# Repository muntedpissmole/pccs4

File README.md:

# PCCS4 Demo

A self-contained demo of the Pissmole Camper Control System — runs on Linux. Lights, reed switches, Sonos, battery/solar, water, and GPS are simulated so you can explore the full web UI (lighting, scenes, home dashboard, system tab).

Reed switches open and close on their own every few hours; the Sonos tile plays through a built-in indie/alternative playlist.

## Install

```bash
git clone -b demo https://github.com/muntedpissmole/pccs4.git ~/pccs-demo
cd ~/pccs-demo
chmod +x scripts/install-demo.sh
sudo ./scripts/install-demo.sh
```

Open `http://<server-ip>:5000/` in a browser.

The installer sets up the Python venv, `requirements-demo.txt`, and a `pccs-demo` systemd service listening on port 5000.

## After install

```bash
sudo systemctl status pccs-demo
sudo journalctl -u pccs-demo -f
```

To make sure there's no errors.

## Update

Use the update script (handles `git pull`, dependency refresh, and config safely):

```bash
cd ~/pccs-demo
chmod +x scripts/update-demo.sh
sudo ./scripts/update-demo.sh
```

**Do not edit `config/pccs.conf` on the server.** The installer writes machine-specific settings (port, `debug = false`, etc.) to `config/pccs.local.conf`, which git ignores. If you need custom settings, edit `pccs.local.conf` and restart the service.

If you previously hit a `git pull` error about `config/pccs.conf`, run `update-demo.sh` once — it resets that file and pulls cleanly.

## Uninstall

Removes the systemd service, Python venv, logs, and firewall rule. The repo directory is kept — delete it manually if you no longer need it.

```bash
cd ~/pccs-demo
chmod +x scripts/uninstall-demo.sh
sudo ./scripts/uninstall-demo.sh
```

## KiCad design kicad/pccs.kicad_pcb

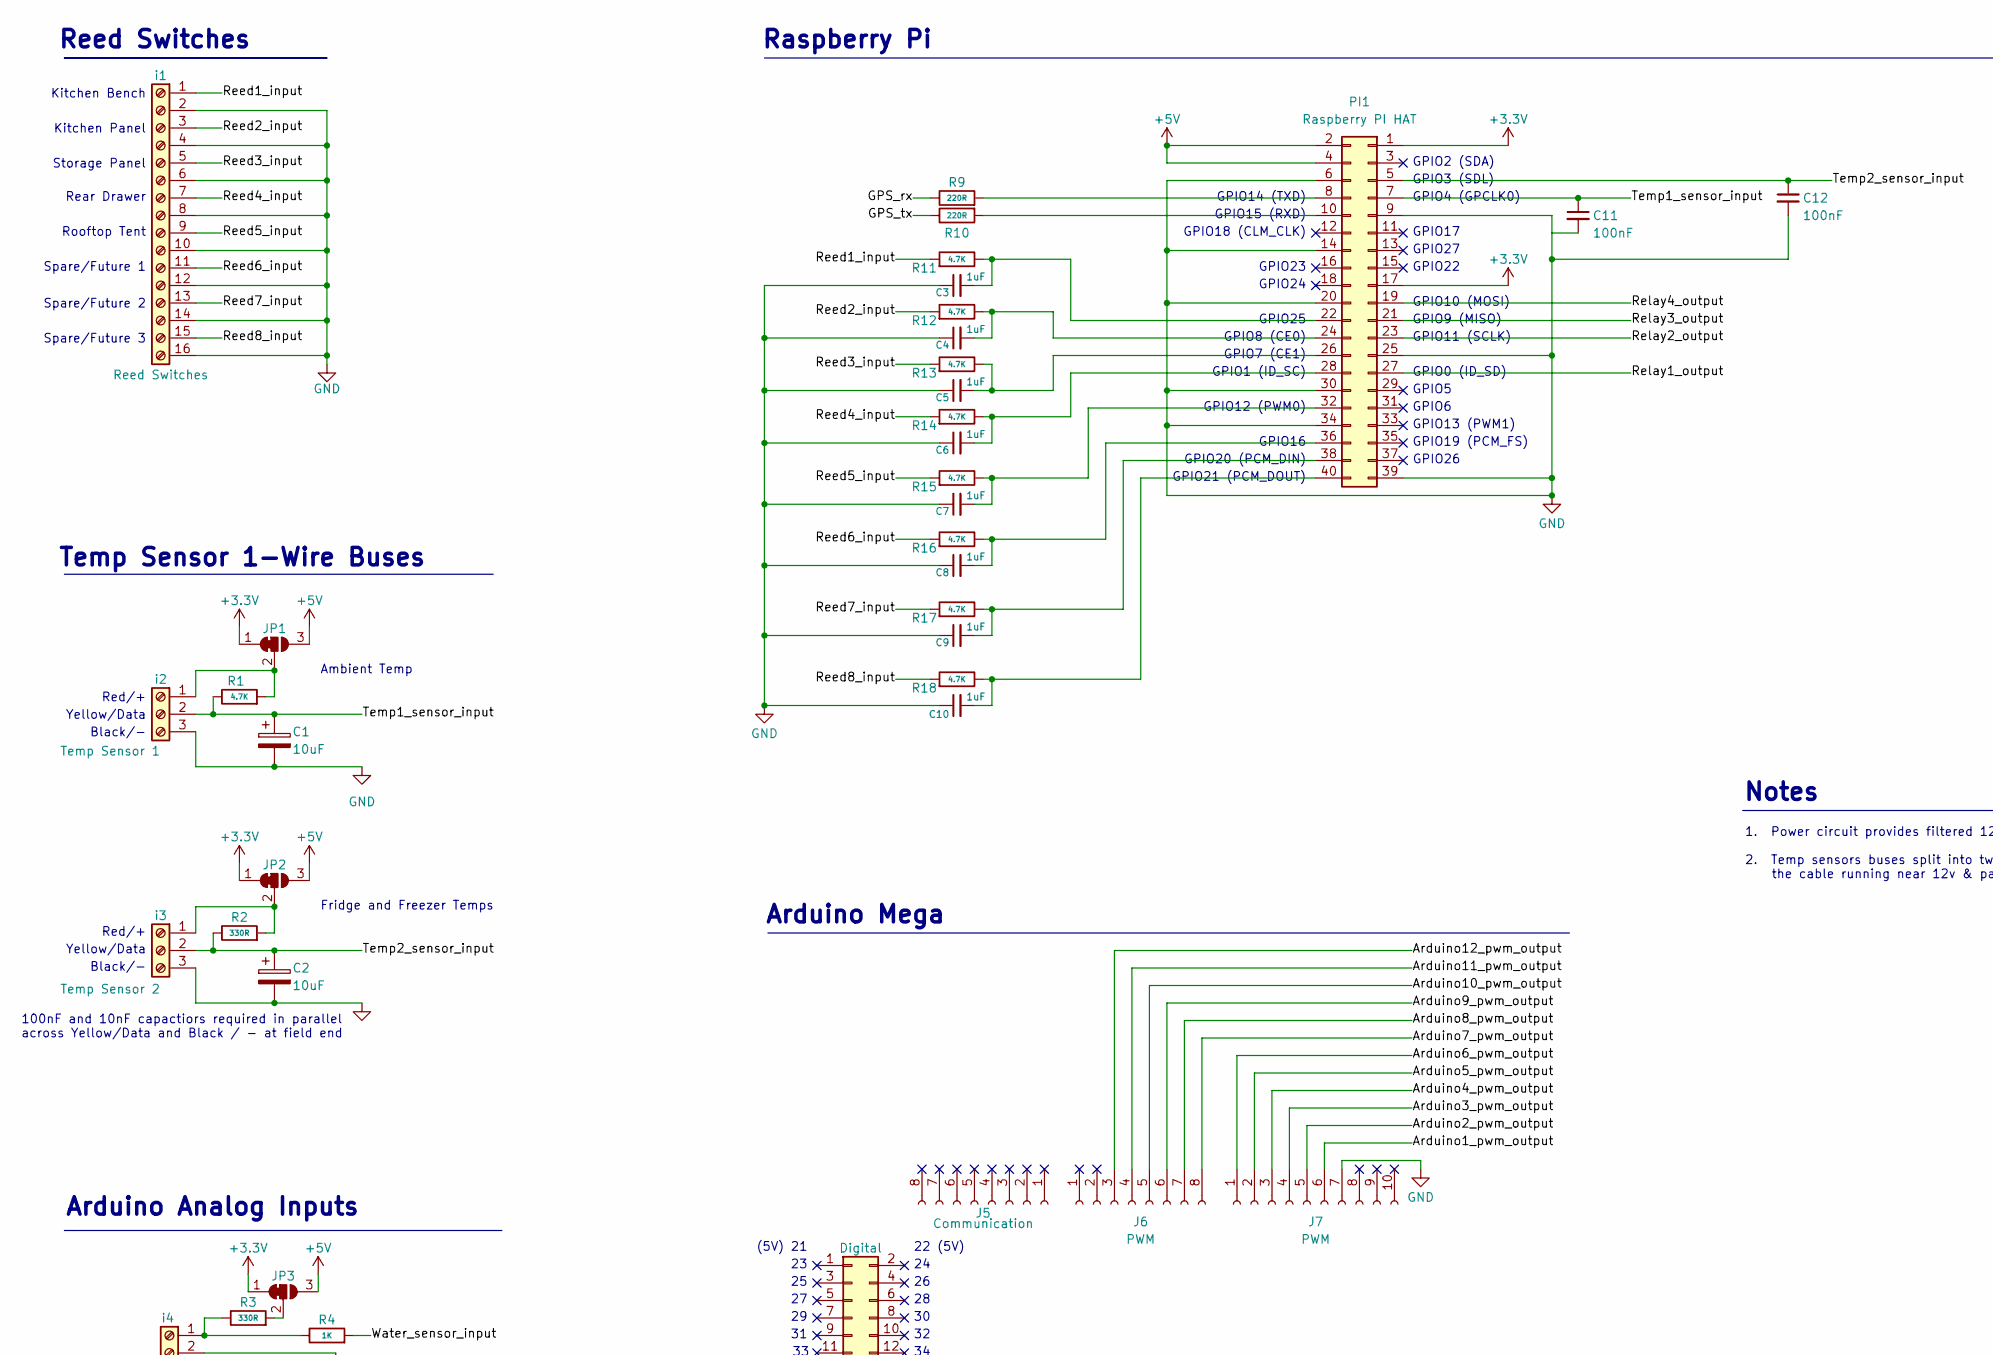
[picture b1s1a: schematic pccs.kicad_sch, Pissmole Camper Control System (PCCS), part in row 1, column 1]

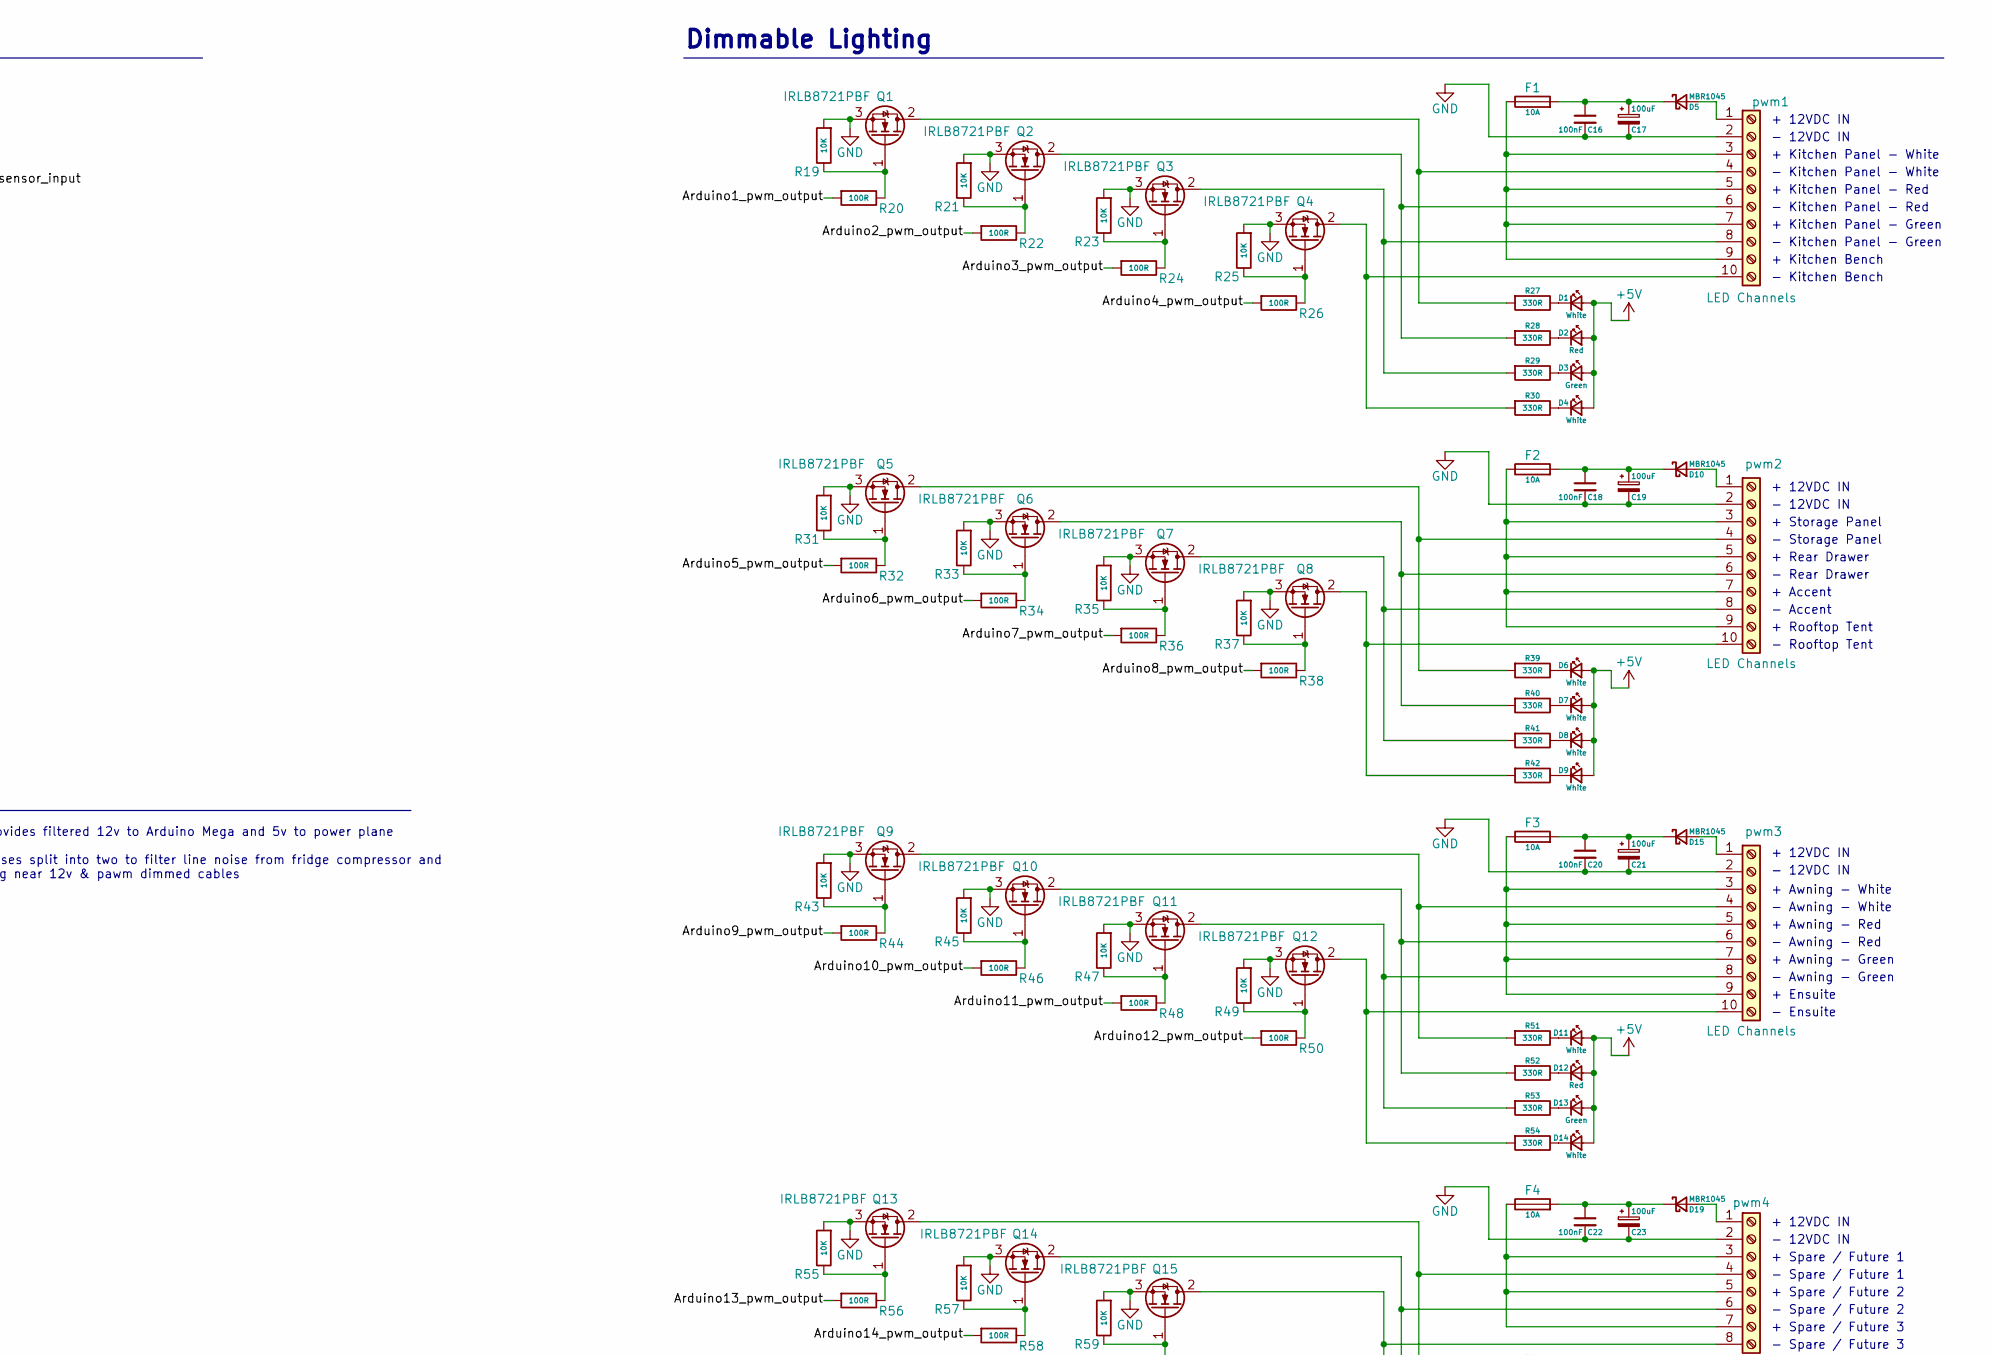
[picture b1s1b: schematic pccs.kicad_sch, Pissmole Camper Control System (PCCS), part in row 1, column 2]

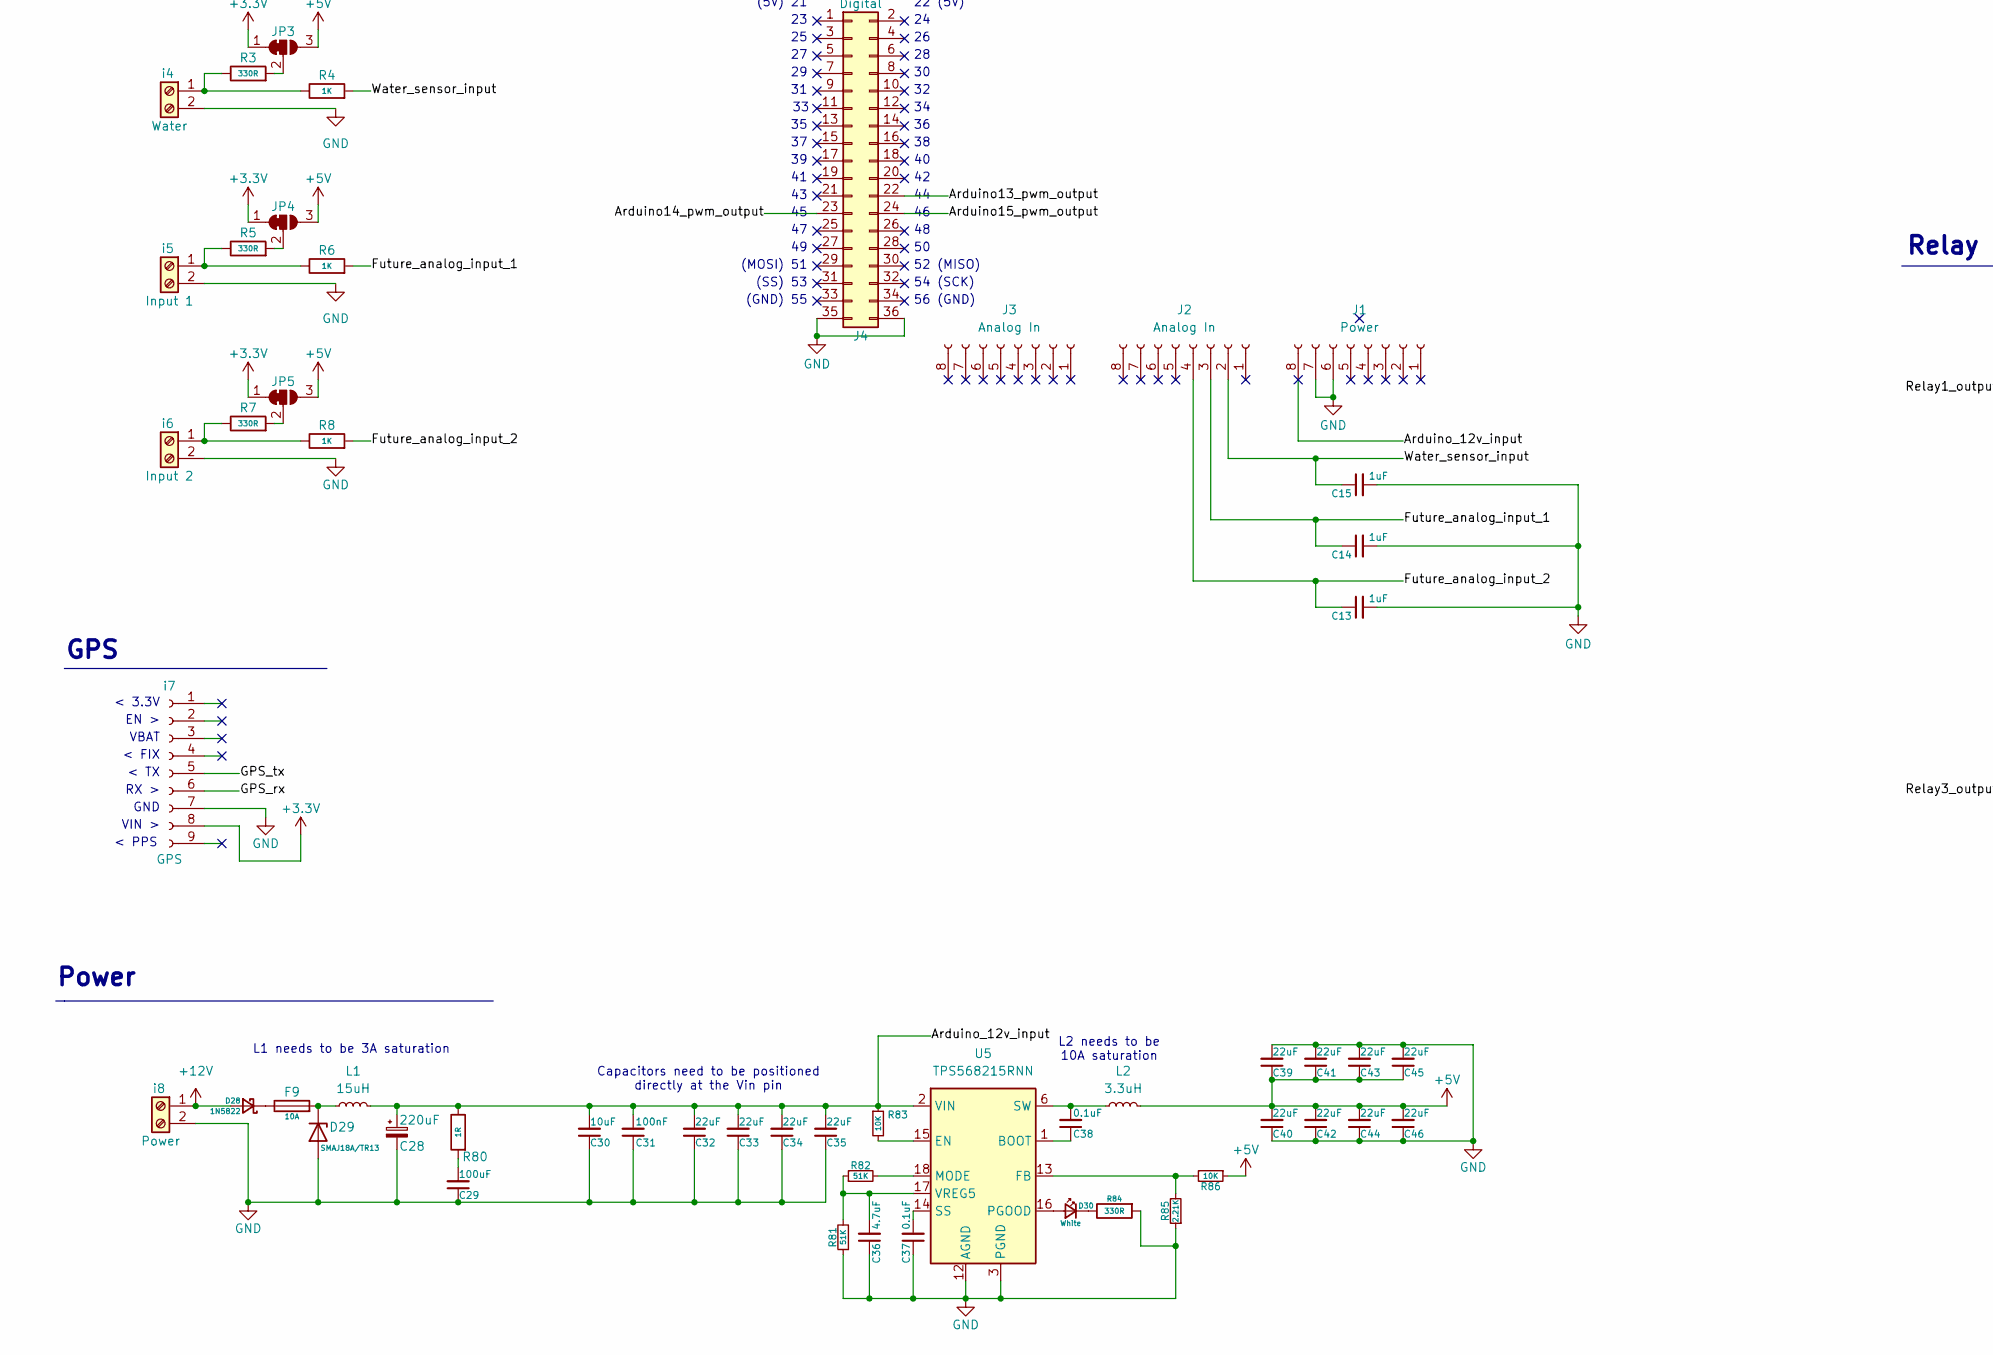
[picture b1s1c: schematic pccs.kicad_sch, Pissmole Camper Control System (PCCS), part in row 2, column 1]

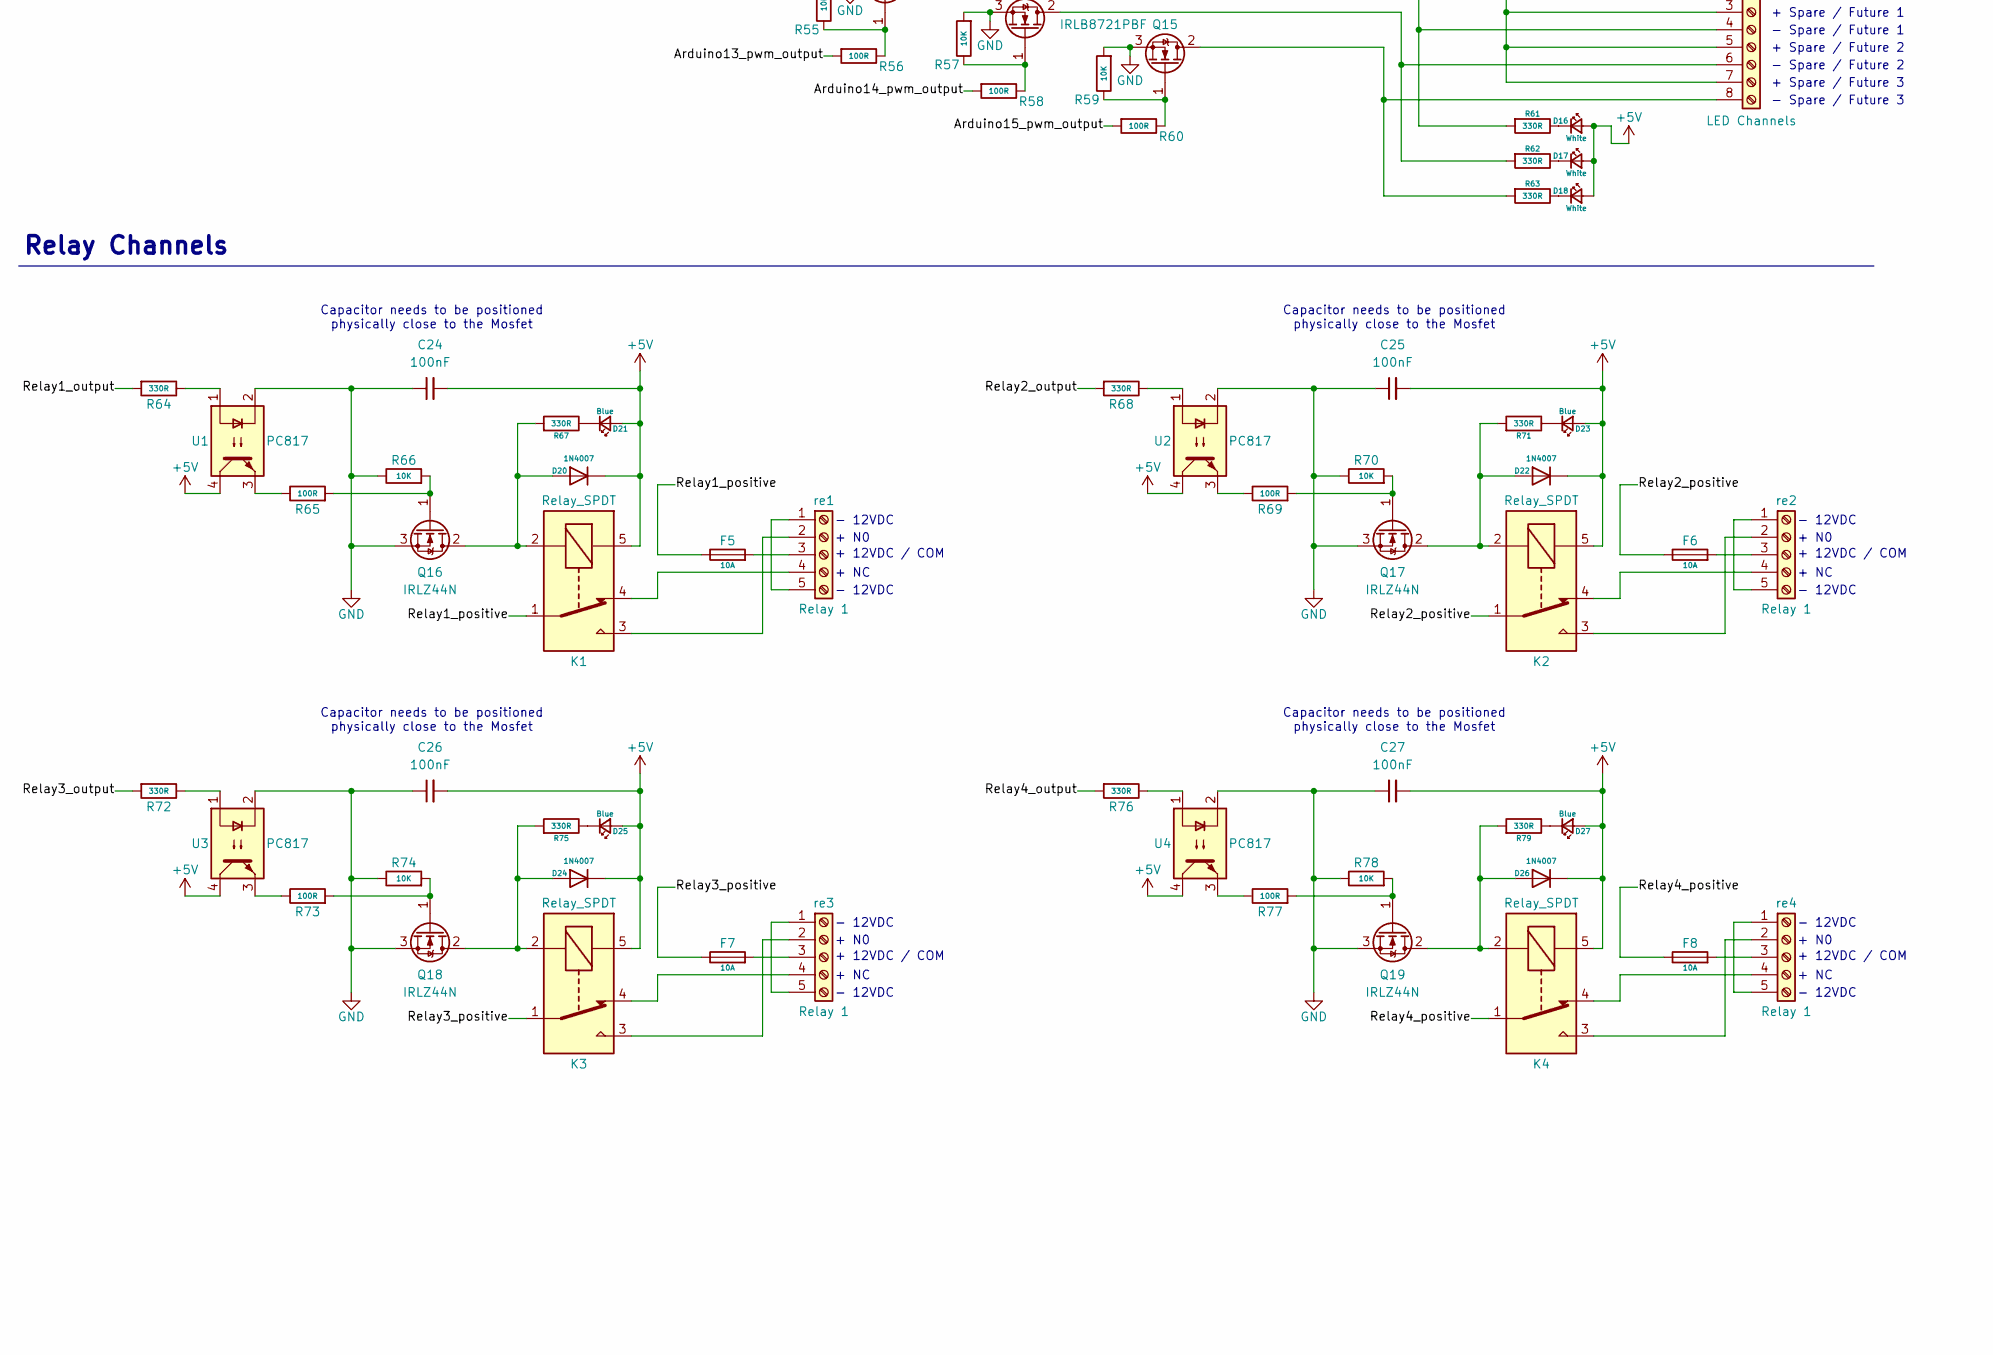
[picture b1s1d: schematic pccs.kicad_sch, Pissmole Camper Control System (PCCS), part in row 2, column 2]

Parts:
C1, C2, C30: 10uF; C_0805_2012Metric; LCSC Part # C15850
C3, C4, C5, C6, C7, C8, C9, C10, C13, C14, C15: 1uF; C_0805_2012Metric; LCSC Part # C53084463
C11, C12, C16, C18, C20, C22, C24, C25, C26, C27, C31: 100nF; C_0805_2012Metric; LCSC Part # C53084462
C17, C19, C21, C23: 100uF; CP_Radial_D6.3mm_P2.50mm; LCSC Part # C165558
C28: 220uF; CP_Radial_D8.0mm_P3.50mm; LCSC Part # C165536
C29: 100uF; C_1210_3225Metric; LCSC Part # C90143
C32, C33, C34, C35, C39, C40, C41, C42, C43, C44, C45, C46: 22uF; C_0805_2012Metric; LCSC Part # C86816
C36: 4.7uF; C_0805_2012Metric; LCSC Part # C1779
C37, C38: 0.1uF; C_0805_2012Metric; LCSC Part # C86041
D1, D4, D6, D7, D8, D9, D11, D14, D16, D17, D18, D30: White; LED_0805_2012Metric; LCSC Part # C84258
D2, D12: Red; LED_0805_2012Metric; LCSC Part # C84256
D3, D13: Green; LED_0805_2012Metric; LCSC Part # C84260
D5, D10, D15, D19: MBR1045; TO-220-2_Vertical; LCSC Part # C260253
D20, D22, D24, D26: 1N4007; D_DO-41_SOD81_P10.16mm_Horizontal; LCSC Part # C84641
D21, D23, D25, D27: Blue; LED_0805_2012Metric; LCSC Part # C84259
D28: 1N5822; TO-220-2_Vertical; LCSC Part # C2476
D29: SMAJ18A/TR13; Nexperia_DSN1608-2_1.6x0.8mm; LCSC Part # C118306
F1, F2, F3, F4, F5, F6, F7, F8, F9: 10A; Fuse_Bourns_MF-RG1000; LCSC Part # C14767
J1: Power; PinSocket_1x08_P2.54mm_Vertical
J2, J3: Analog In; PinSocket_1x08_P2.54mm_Vertical
J4: Digital; PinSocket_2x18_P2.54mm_Vertical
J5: Communication; PinSocket_1x08_P2.54mm_Vertical
J6: PWM; PinSocket_1x08_P2.54mm_Vertical
J7: PWM; PinSocket_1x10_P2.54mm_Vertical
JP1, JP2, JP3, JP4, JP5: SolderJumper_3_Bridged12; SolderJumper-3_P1.3mm_Bridged12_Pad1.0x1.5mm
K1, K2, K3, K4: Relay_SPDT; Relay_SPDT_SANYOU_SRD_Series_Form_C; LCSC Part # C35449
L1: 15uH; L_10.4x10.4_H4.8; LCSC Part # C16113
L2: 3.3uH; L_SXN_SMDRI127; LCSC Part # C24550
PI1: Raspberry PI HAT; PinSocket_2x20_P2.54mm_Vertical
Q1, Q2, Q3, Q4, Q5, Q6, Q7, Q8, Q9, Q10, Q11, Q12, Q13, Q14, Q15: IRLB8721PBF; TO-220-3_Vertical; LCSC Part # C148140
Q16, Q17, Q18, Q19: IRLZ44N; TO-220-3_Vertical; LCSC Part # C38774
R1, R11, R12, R13, R14, R15, R16, R17, R18: 4.7K; R_0805_2012Metric; LCSC Part # C17673
R2, R3, R5, R7, R27, R28, R29, R30, R39, R40, R41, R42, R51, R52, R53, R54, R61, R62, R63, R64, R67, R68, R71, R72, R75, R76, R79, R84: 330R; R_0805_2012Metric; LCSC Part # C17630
R4, R6, R8: 1K; R_0805_2012Metric; LCSC Part # C17513
R9, R10: 220R; R_0805_2012Metric; LCSC Part # C17557
R19, R21, R23, R25, R31, R33, R35, R37, R43, R45, R47, R49, R55, R57, R59, R66, R70, R74, R78, R83, R86: 10K; R_0805_2012Metric; LCSC Part # C17414
R20, R22, R24, R26, R32, R34, R36, R38, R44, R46, R48, R50, R56, R58, R60, R65, R69, R73, R77: 100R; R_0805_2012Metric; LCSC Part # C17408
R80: 1R; R_0805_2012Metric; LCSC Part # C25271
R81, R82: 51K; R_0805_2012Metric; LCSC Part # C17737
R85: 2.21K; R_0805_2012Metric; LCSC Part # C17518
U1, U2, U3, U4: PC817; DIP-4_W7.62mm; LCSC Part # C41807
U5: TPS568215RNN; Texas_RNN0018A; LCSC Part # C473367
i1: Reed Switches; TerminalBlock_Phoenix_MKDS-1,5-16-5.08_1x16_P5.08mm_Horizon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; LCSC Part # C5482573
i2: Temp Sensor 1; TerminalBlock_Phoenix_MKDS-1,5-3-5.08_1x03_P5.08mm_Horizont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; LCSC Part # C480509
i3: Temp Sensor 2; TerminalBlock_Phoenix_MKDS-1,5-3-5.08_1x03_P5.08mm_Horizont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; LCSC Part # C480509
i4: Water; TerminalBlock_Phoenix_MKDS-1,5-2-5.08_1x02_P5.08mm_Horizont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; LCSC Part # C480503
i5: Input 1; TerminalBlock_Phoenix_MKDS-1,5-2-5.08_1x02_P5.08mm_Horizont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; LCSC Part # C480503
i6: Input 2; TerminalBlock_Phoenix_MKDS-1,5-2-5.08_1x02_P5.08mm_Horizont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; LCSC Part # C480503
i7: GPS; PinSocket_1x09_P2.54mm_Vertical; LCSC Part # C2932673
i8: Power; TerminalBlock_Phoenix_MKDS-1,5-2-5.08_1x02_P5.08mm_Horizont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; LCSC Part # C480503
pwm1, pwm2, pwm3: LED Channels; TerminalBlock_Phoenix_MKDS-1,5-10-5.08_1x10_P5.08mm_Horizon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; LCSC Part # C3019624
pwm4: LED Channels; TerminalBlock_Phoenix_MKDS-1,5-8-5.08_1x08_P5.08mm_Horizont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; LCSC Part # C480562
re1, re2, re3, re4: Relay 1; TerminalBlock_Phoenix_MKDS-3-5-5.08_1x05_P5.08mm_Horizontal; LCSC Part # C457197

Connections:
+3.3V: JP1.1 (A), JP2.1 (A), JP3.1 (A), JP4.1 (A), JP5.1 (A), PI1.1, PI1.17, i7.8
+5V: C24.2, C25.2, C26.2, C27.2, C39.1, C40.2, C41.1, C42.2, C43.1, C44.2, C45.1, C46.2, D1.2 (A), D2.2 (A), D3.2 (A), D4.2 (A), D6.2 (A), D7.2 (A), D8.2 (A), D9.2 (A), D11.2 (A), D12.2 (A), D13.2 (A), D14.2 (A), D16.2 (A), D17.2 (A), D18.2 (A), D20.1 (K), D21.2 (A), D22.1 (K), D23.2 (A), D24.1 (K), D25.2 (A), D26.1 (K), D27.2 (A), JP1.3 (B), JP2.3 (B), JP3.3 (B), JP4.3 (B), JP5.3 (B), K1.5, K2.5, K3.5, K4.5, L2.2, PI1.2, PI1.4, R86.1, U1.4, U2.4, U3.4, U4.4
+12V: D28.2 (A), i8.1
/Arduino1_pwm_output: J7.6, R20.2
/Arduino2_pwm_output: J7.5, R22.2
/Arduino3_pwm_output: J7.4, R24.2
/Arduino4_pwm_output: J7.3, R26.2
/Arduino5_pwm_output: J7.2, R32.2
/Arduino6_pwm_output: J7.1, R34.2
/Arduino7_pwm_output: J6.8, R36.2
/Arduino8_pwm_output: J6.7, R38.2
/Arduino9_pwm_output: J6.6, R44.2
/Arduino10_pwm_output: J6.5, R46.2
/Arduino11_pwm_output: J6.4, R48.2
/Arduino12_pwm_output: J6.3, R50.2
/Arduino13_pwm_output: J4.22, R56.2
/Arduino14_pwm_output: J4.23, R58.2
/Arduino15_pwm_output: J4.24, R60.2
/Arduino_12v_input: C28.1, C30.2, C31.2, C32.2, C33.2, C34.2, C35.2, J1.8, L1.2, R80.1, R83.1, U5.2 (VIN), U5.11 (VIN)
/Future_analog_input_1: C14.1, J2.3, R6.2
/Future_analog_input_2: C13.1, J2.4, R8.2
/GPS_rx: R9.1, i7.6
/GPS_tx: R10.1, i7.5
/Reed1_input: R11.2, i1.1
/Reed2_input: R12.2, i1.3
/Reed3_input: R13.2, i1.5
/Reed4_input: R14.2, i1.7
/Reed5_input: R15.2, i1.9
/Reed6_input: R16.2, i1.11
/Reed7_input: R17.2, i1.13
/Reed8_input: R18.2, i1.15
/Relay1_output: PI1.27, R64.2
/Relay1_positive: F5.1, K1.1
/Relay2_output: PI1.23, R68.2
/Relay2_positive: F6.1, K2.1
/Relay3_output: PI1.21, R72.2
/Relay3_positive: F7.1, K3.1
/Relay4_output: PI1.19, R76.2
/Relay4_positive: F8.1, K4.1
/Temp1_sensor_input: C1.1, C11.1, PI1.7, R1.1, i2.2
/Temp2_sensor_input: C2.1, C12.1, PI1.5, R2.1, i3.2
/Water_sensor_input: C15.1, J2.2, R4.2
GND: C1.2, C2.2, C3.1, C4.1, C5.1, C6.1, C7.1, C8.1, C9.1, C10.1, C11.2, C12.2, C13.2, C14.2, C15.2, C16.2, C17.2, C18.2, C19.2, C20.2, C21.2, C22.2, C23.2, C24.1, C25.1, C26.1, C27.1, C28.2, C29.1, C30.1, C31.1, C32.1, C33.1, C34.1, C35.1, C36.1, C37.1, C39.2, C40.1, C41.2, C42.1, C43.2, C44.1, C45.2, C46.1, D29.2 (A), J1.6, J1.7, J4.35, J4.36, J7.7, PI1.6, PI1.9, PI1.14, PI1.20, PI1.25, PI1.30, PI1.34, PI1.39, Q1.3 (S), Q2.3 (S), Q3.3 (S), Q4.3 (S), Q5.3 (S), Q6.3 (S), Q7.3 (S), Q8.3 (S), Q9.3 (S), Q10.3 (S), Q11.3 (S), Q12.3 (S), Q13.3 (S), Q14.3 (S), Q15.3 (S), Q16.3 (S), Q17.3 (S), Q18.3 (S), Q19.3 (S), R19.2, R21.2, R23.2, R25.2, R31.2, R33.2, R35.2, R37.2, R43.2, R45.2, R47.2, R49.2, R55.2, R57.2, R59.2, R66.1, R70.1, R74.1, R78.1, R81.1, R84.2, R85.1, U1.2, U2.2, U3.2, U4.2, U5.3 (PGND), U5.4 (PGND), U5.5 (PGND), U5.8 (PGND), U5.9 (PGND), U5.10 (PGND), U5.12 (AGND), i1.2, i1.4, i1.6, i1.8, i1.10, i1.12, i1.14, i1.16, i2.3, i3.3, i4.2, i5.2, i6.2, i7.7, i8.2, pwm1.2, pwm2.2, pwm3.2, pwm4.2
unnamed: C29.2, R80.2
unnamed: C38.2, L2.1, U5.6 (SW), U5.7 (SW)
unnamed: D1.1 (K), R27.1
unnamed: D2.1 (K), R28.1
unnamed: D3.1 (K), R29.1
unnamed: D4.1 (K), R30.1
unnamed: D5.2 (A), pwm1.1
unnamed: C16.1, C17.1, D5.1 (K), F1.2
unnamed: D6.1 (K), R39.1
unnamed: D7.1 (K), R40.1
unnamed: D8.1 (K), R41.1
unnamed: D9.1 (K), R42.1
unnamed: D10.2 (A), pwm2.1
unnamed: C18.1, C19.1, D10.1 (K), F2.2
unnamed: D11.1 (K), R51.1
unnamed: D12.1 (K), R52.1
unnamed: D13.1 (K), R53.1
unnamed: D14.1 (K), R54.1
unnamed: D15.2 (A), pwm3.1
unnamed: C20.1, C21.1, D15.1 (K), F3.2
unnamed: D16.1 (K), R61.1
unnamed: D17.1 (K), R62.1
unnamed: D18.1 (K), R63.1
unnamed: D19.2 (A), pwm4.1
unnamed: C22.1, C23.1, D19.1 (K), F4.2
unnamed: D20.2 (A), K1.2, Q16.2 (D), R67.2
unnamed: D21.1 (K), R67.1
unnamed: D22.2 (A), K2.2, Q17.2 (D), R71.2
unnamed: D23.1 (K), R71.1
unnamed: D24.2 (A), K3.2, Q18.2 (D), R75.2
unnamed: D25.1 (K), R75.1
unnamed: D26.2 (A), K4.2, Q19.2 (D), R79.2
unnamed: D27.1 (K), R79.1
unnamed: D28.1 (K), F9.1
unnamed: D29.1 (K), F9.2, L1.1
unnamed: D30.2 (A), U5.16 (PGOOD)
unnamed: D30.1 (K), R84.1
unnamed: JP1.2 (C), R1.2, i2.1
unnamed: JP2.2 (C), R2.2, i3.1
unnamed: JP3.2 (C), R3.2
unnamed: JP4.2 (C), R5.2
unnamed: JP5.2 (C), R7.2
unnamed: PI1.8, R9.2
unnamed: PI1.10, R10.2
unnamed: C3.2, PI1.22, R11.1
unnamed: C4.2, PI1.24, R12.1
unnamed: C5.2, PI1.26, R13.1
unnamed: C6.2, PI1.28, R14.1
unnamed: C7.2, PI1.32, R15.1
unnamed: C8.2, PI1.36, R16.1
unnamed: C9.2, PI1.38, R17.1
unnamed: C10.2, PI1.40, R18.1
unnamed: Q1.2 (D), R27.2, pwm1.4
unnamed: Q1.1 (G), R19.1, R20.1
unnamed: Q2.2 (D), R28.2, pwm1.6
unnamed: Q2.1 (G), R21.1, R22.1
unnamed: Q3.2 (D), R29.2, pwm1.8
unnamed: Q3.1 (G), R23.1, R24.1
unnamed: Q4.2 (D), R30.2, pwm1.10
unnamed: Q4.1 (G), R25.1, R26.1
unnamed: Q5.2 (D), R39.2, pwm2.4
unnamed: Q5.1 (G), R31.1, R32.1
unnamed: Q6.2 (D), R40.2, pwm2.6
unnamed: Q6.1 (G), R33.1, R34.1
unnamed: Q7.2 (D), R41.2, pwm2.8
unnamed: Q7.1 (G), R35.1, R36.1
unnamed: Q8.2 (D), R42.2, pwm2.10
unnamed: Q8.1 (G), R37.1, R38.1
unnamed: Q9.2 (D), R51.2, pwm3.4
unnamed: Q9.1 (G), R43.1, R44.1
unnamed: Q10.2 (D), R52.2, pwm3.6
unnamed: Q10.1 (G), R45.1, R46.1
unnamed: Q11.2 (D), R53.2, pwm3.8
unnamed: Q11.1 (G), R47.1, R48.1
unnamed: Q12.2 (D), R54.2, pwm3.10
unnamed: Q12.1 (G), R49.1, R50.1
unnamed: Q13.2 (D), R61.2, pwm4.4
unnamed: Q13.1 (G), R55.1, R56.1
unnamed: Q14.2 (D), R62.2, pwm4.6
unnamed: Q14.1 (G), R57.1, R58.1
unnamed: Q15.2 (D), R63.2, pwm4.8
unnamed: Q15.1 (G), R59.1, R60.1
unnamed: Q16.1 (G), R65.2, R66.2
unnamed: Q17.1 (G), R69.2, R70.2
unnamed: Q18.1 (G), R73.2, R74.2
unnamed: Q19.1 (G), R77.2, R78.2
unnamed: R64.1, U1.1
unnamed: R65.1, U1.3
unnamed: R68.1, U2.1
unnamed: R69.1, U2.3
unnamed: R72.1, U3.1
unnamed: R73.1, U3.3
unnamed: R76.1, U4.1
unnamed: R77.1, U4.3
unnamed: C38.1, U5.1 (BOOT)
unnamed: R83.2, U5.15 (EN)
unnamed: R85.2, R86.2, U5.13 (FB)
unnamed: R82.2, U5.18 (MODE)
unnamed: C37.2, U5.14 (SS)
unnamed: C36.2, R81.2, R82.1, U5.17 (VREG5)
unnamed: R3.1, R4.1, i4.1
unnamed: R5.1, R6.1, i5.1
unnamed: R7.1, R8.1, i6.1
unnamed: F1.1, pwm1.3, pwm1.5, pwm1.7, pwm1.9
unnamed: F2.1, pwm2.3, pwm2.5, pwm2.7, pwm2.9
unnamed: F3.1, pwm3.3, pwm3.5, pwm3.7, pwm3.9
unnamed: F4.1, pwm4.3, pwm4.5, pwm4.7
unnamed: re1.1, re1.5
unnamed: K1.3, re1.2
unnamed: F5.2, re1.3
unnamed: K1.4, re1.4
unnamed: re2.1, re2.5
unnamed: K2.3, re2.2
unnamed: F6.2, re2.3
unnamed: K2.4, re2.4
unnamed: re3.1, re3.5
unnamed: K3.3, re3.2
unnamed: F7.2, re3.3
unnamed: K3.4, re3.4
unnamed: re4.1, re4.5
unnamed: K4.3, re4.2
unnamed: F8.2, re4.3
unnamed: K4.4, re4.4

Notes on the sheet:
+ Awning - White
< FIX
GPIO1 (ID_SC)
- Spare / Future 3
Capacitor needs to be positioned physically close to the Mosfet
- 12VDC
Capacitors need to be positioned directly at the Vin pin
- 12VDC IN
+ N0
GPIO12 (PWM0)
Rooftop Tent
+ 12VDC / COM
Temp Sensor 1-Wire Buses
GPIO15 (RXD)
GPIO22
GPIO23
+ 12VDC IN
- Kitchen Panel - Red
Spare/Future 3
GPIO20 (PCM_DIN)
100nF and 10nF capactiors required in parallel across Yellow/Data and Black / - at field end
1. Power circuit provides filtered 12v to Arduino Mega and 5v to power plane 2. Temp sensors buses split into two to filter line noise from fridge compressor and the cable running near 12v & pawm dimmed cables
- Rear Drawer
Arduino Mega
(MOSI) 51
+ Kitchen Bench
- Accent
(GND) 55
(5V) 21
GPIO25
< TX
GPIO27
GPIO11 (SCLK)
VIN >
+ Storage Panel
GPS
+ Ensuite
Yellow/Data
- Kitchen Bench
GPIO7 (CE1)

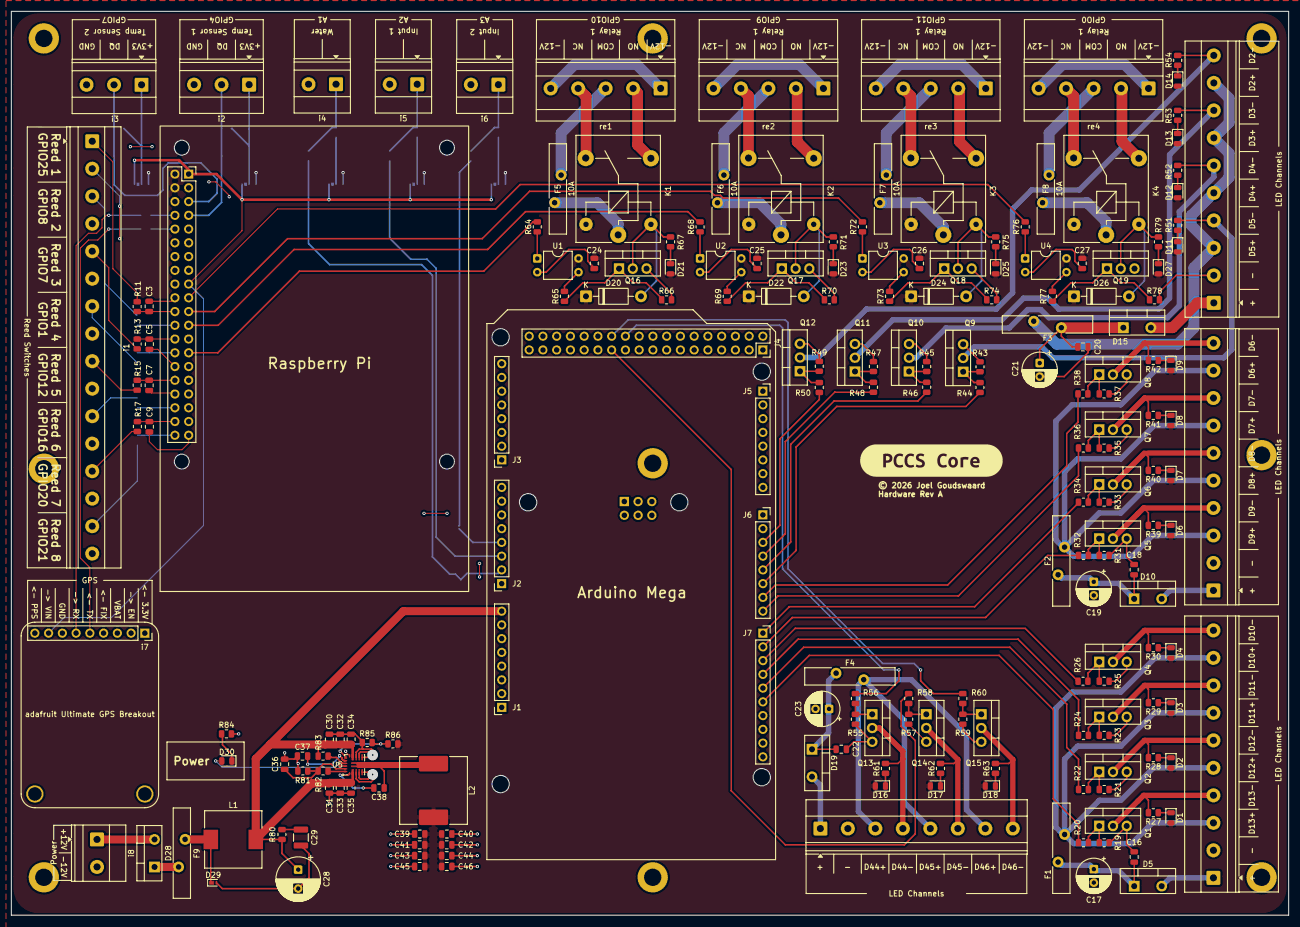
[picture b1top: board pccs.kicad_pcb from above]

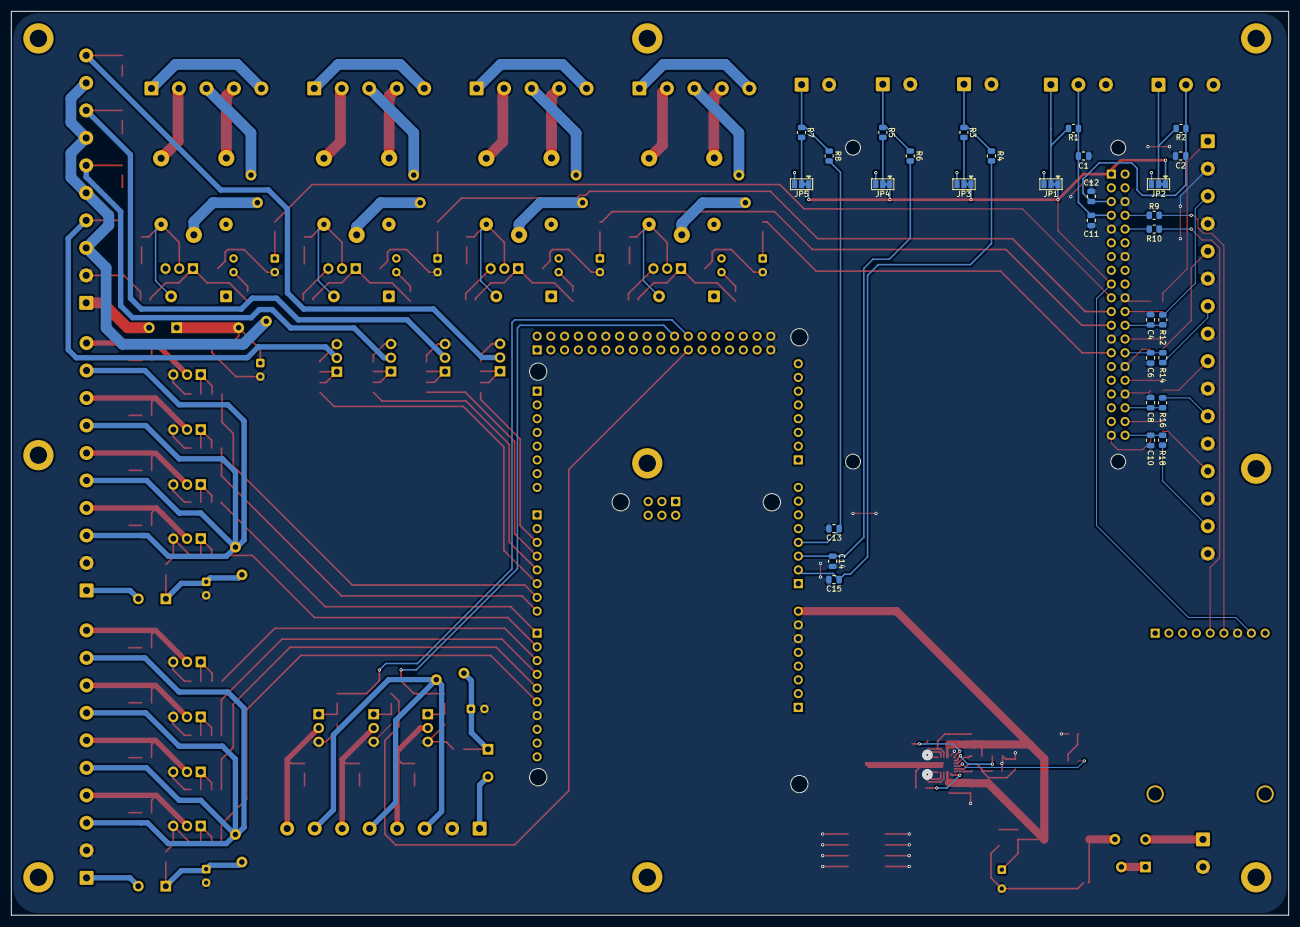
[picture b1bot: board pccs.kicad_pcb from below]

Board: 2 copper layers, 236.0 x 167.0 mm, 234 parts (31 on the bottom side), 166 nets.

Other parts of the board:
AR1: Arduino_Mega2560_R3_Shield
GPS: adafruit Ultimate GPS Breakout; adafruit_ultimate_gps_breakout
PI1#2: Raspberry Pi; RaspberryPi_4_Upside_Down
kibuzzard-6A4B41A9: G***; kibuzzard-6A4B41A9

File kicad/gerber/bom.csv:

Designator,Footprint,Quantity,Value,LCSC Part #
AR1,Arduino_Mega2560_R3_Shield,1,Arduino_Mega2560_R3_Shield,
"C1, C2, C30",0805,3,10uF,C15850
"C10, C13, C14, C15, C3, C4, C5, C6, C7, C8, C9",0805,11,1uF,C53084463
"C11, C12, C16, C18, C20, C22, C24, C25, C26, C27, C31",0805,11,100nF,C53084462
"C17, C19, C21, C23",CP_Radial_D6.3mm_P2.50mm,4,100uF,C165558
C28,CP_Radial_D8.0mm_P3.50mm,1,220uF,C165536
C29,1210,1,100uF,C90143
"C32, C33, C34, C35, C39, C40, C41, C42, C43, C44, C45, C46",0805,12,22uF,C86816
C36,0805,1,4.7uF,C1779
"C37, C38",0805,2,0.1uF,C86041
"D1, D11, D14, D16, D17, D18, D30, D4, D6, D7, D8, D9",0805,12,White,C84258
"D10, D15, D19, D5",TO-220-2_Vertical,4,MBR1045,C260253
"D12, D2",0805,2,Red,C84256
"D13, D3",0805,2,Green,C84260
"D20, D22, D24, D26",D_DO-41_SOD81_P10.16mm_Horizontal,4,1N4007,C84641
"D21, D23, D25, D27",0805,4,Blue,C84259
D28,TO-220-2_Vertical,1,1N5822,C2476
D29,Nexperia_DSN1608-2_1.6x0.8mm,1,SMAJ18A/TR13,C118306
"F1, F2, F3, F4, F5, F6, F7, F8, F9",Fuse_Bourns_MF-RG1000,9,10A,C14767
GPS,adafruit_ultimate_gps_breakout,1,adafruit Ultimate GPS Breakout,
I1,"TerminalBlock_Phoenix_MKDS-1,5-16-5.08_1x16_P5.08mm_Horizontal",1,Reed Switches,C5482573
I2,"TerminalBlock_Phoenix_MKDS-1,5-3-5.08_1x03_P5.08mm_Horizontal",1,Temp Sensor 1,C480509
I3,"TerminalBlock_Phoenix_MKDS-1,5-3-5.08_1x03_P5.08mm_Horizontal",1,Temp Sensor 2,C480509
I4,"TerminalBlock_Phoenix_MKDS-1,5-2-5.08_1x02_P5.08mm_Horizontal",1,Water,C480503
I5,"TerminalBlock_Phoenix_MKDS-1,5-2-5.08_1x02_P5.08mm_Horizontal",1,Input 1,C480503
I6,"TerminalBlock_Phoenix_MKDS-1,5-2-5.08_1x02_P5.08mm_Horizontal",1,Input 2,C480503
I7,PinSocket_1x09_P2.54mm_Vertical,1,GPS,C2932673
I8,"TerminalBlock_Phoenix_MKDS-1,5-2-5.08_1x02_P5.08mm_Horizontal",1,Power,C480503
"K1, K2, K3, K4",Relay_SPDT_SANYOU_SRD_Series_Form_C,4,Relay_SPDT,C35449
L1,L_10.4x10.4_H4.8,1,15uH,C16113
L2,L_SXN_SMDRI127,1,3.3uH,C24550
PI1_2,RaspberryPi_4_Upside_Down,1,Raspberry Pi,
"PWM1, PWM2, PWM3","TerminalBlock_Phoenix_MKDS-1,5-10-5.08_1x10_P5.08mm_Horizontal",3,LED Channels,1803507
PWM4,"TerminalBlock_Phoenix_MKDS-1,5-8-5.08_1x08_P5.08mm_Horizontal",1,LED Channels,C480562
"Q1, Q10, Q11, Q12, Q13, Q14, Q15, Q2, Q3, Q4, Q5, Q6, Q7, Q8, Q9",TO-220-3_Vertical,15,IRLB8721PBF,C148140
"Q16, Q17, Q18, Q19",TO-220-3_Vertical,4,IRLZ44N,C38774
"R1, R11, R12, R13, R14, R15, R16, R17, R18",0805,9,4.7K,C17673
"R10, R9",0805,2,220R,C17557
"R19, R21, R23, R25, R31, R33, R35, R37, R43, R45, R47, R49, R55, R57, R59, R66, R70, R74, R78, R83, R86",0805,21,10K,C17414
"R2, R27, R28, R29, R3, R30, R39, R40, R41, R42, R5, R51, R52, R53, R54, R61, R62, R63, R64, R67, R68, R7, R71, R72, R75, R76, R79, R84",0805,28,330R,C17630
"R20, R22, R24, R26, R32, R34, R36, R38, R44, R46, R48, R50, R56, R58, R60, R65, R69, R73, R77",0805,19,100R,C17408
"R4, R6, R8",0805,3,1K,C17513
R80,0805,1,1R,C25271
"R81, R82",0805,2,51K,C17737
R85,0805,1,2.21K,C17518
"RE1, RE2, RE3, RE4",TerminalBlock_Phoenix_MKDS-3-5-5.08_1x05_P5.08mm_Horizontal,4,Relay 1,C457197
"U1, U2, U3, U4",DIP-4_W7.62mm,4,PC817,C41807
U5,Texas_RNN0018A,1,TPS568215RNN,C473367

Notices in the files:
kicad/pccs.kicad_pcb:
© 2026 Joel Goudswaard
